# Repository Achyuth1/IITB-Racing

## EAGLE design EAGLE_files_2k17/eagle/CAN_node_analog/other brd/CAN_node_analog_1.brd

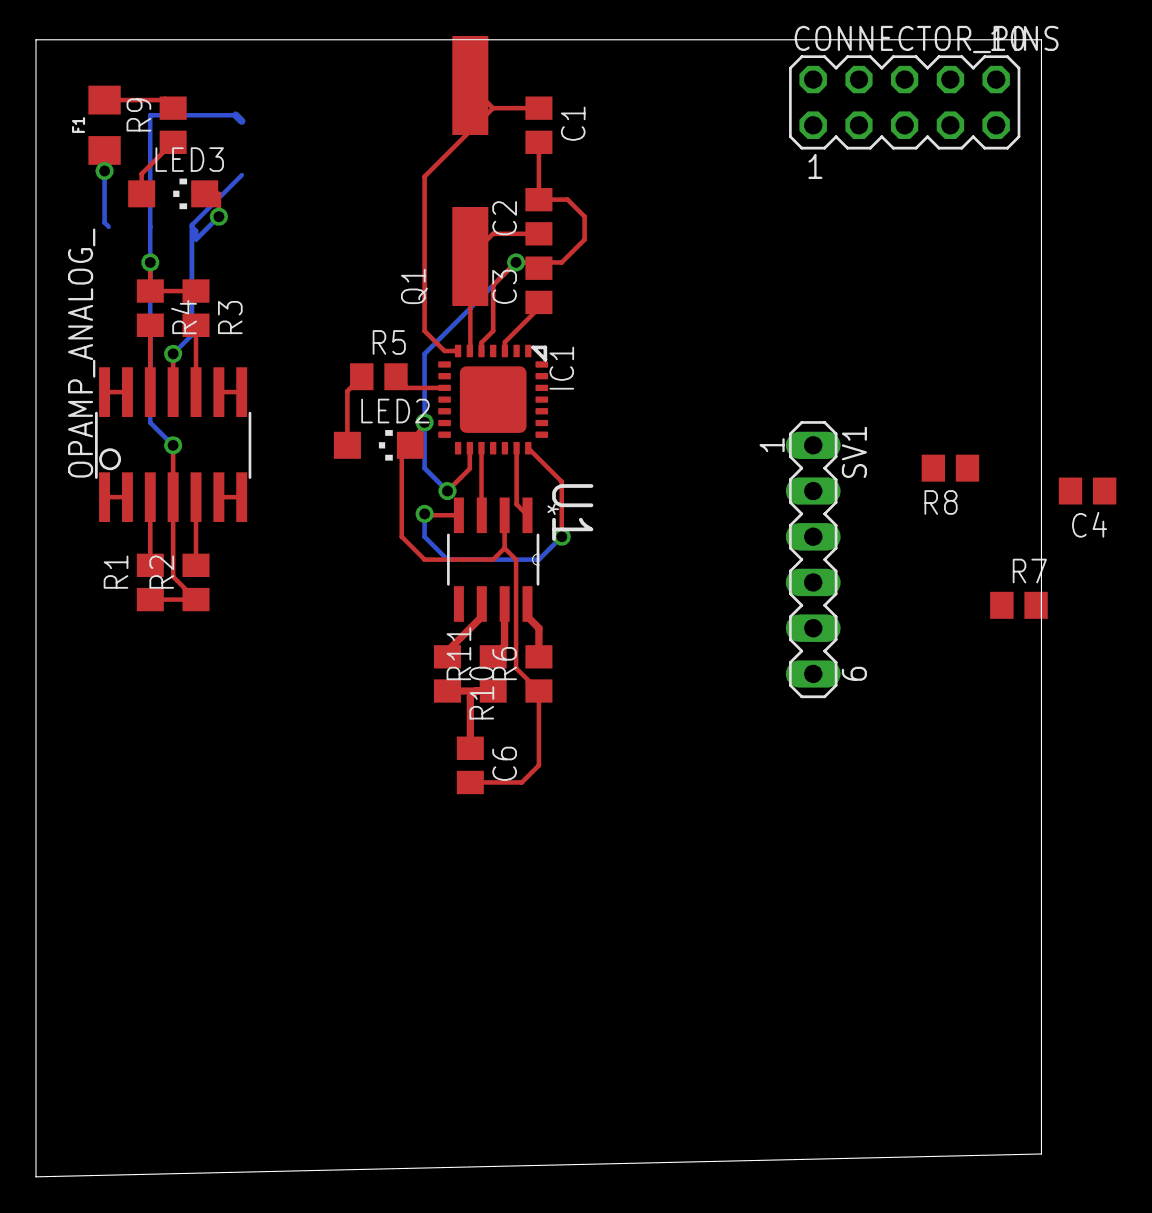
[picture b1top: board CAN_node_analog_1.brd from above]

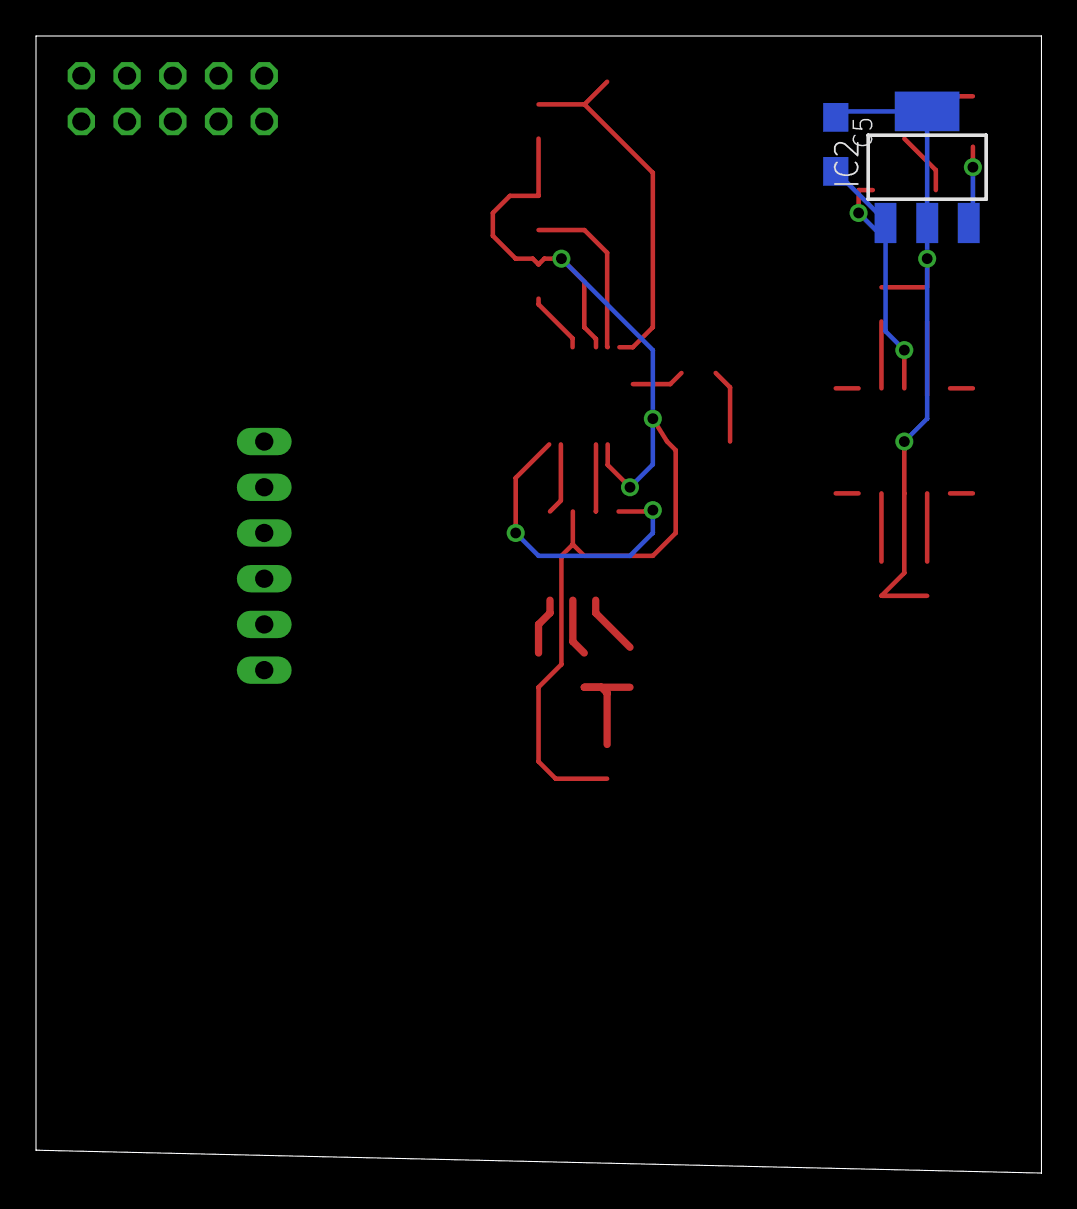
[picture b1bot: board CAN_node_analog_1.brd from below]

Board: 2 copper layers, 55.9 x 63.2 mm, 27 parts (2 on the bottom side), 29 nets.

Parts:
C1, C2, C4: 22pF; C0805
C3, C6: 10uF; C0805
C5: SMC_A
CONNECTOR_PINS: MA05-2
F1: 6V/0.5A; 1206
IC1: MICROCHIP_PIC18F2580-I/ML; MICROCHIP_QFN28-ML_6X6MM
IC2: LM1117IMPX-ADJ; SOT223
LED2, LED3: CHIPLED_1206
OPAMP_ANALOG_: ADWAITFS_LMC6464; ADWAITFS_SO14_LONGPADS
Q1: CSM-7X-DU
R1, R2, R3, R4: 47k; R0805
R5, R9: 1k; R0805
R6: 4k7; R0805
R7: 470; R0805
R8: 10k; R0805
R10, R11: 60E; R0805
SV1: MA06-1
U1: TEXAS-INSTRUMENTS_BY_ELEMENT14_BATCH_1_SN65HVD105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; TEXAS-INSTRUMENTS_BY_ELEMENT14_BATCH_1_SOIC127P600X175-8N

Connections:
5V: C5.+, CONNECTOR_PINS.3, IC1.17, IC2.2, IC2.TAB, OPAMP_ANALOG_.4, R1.1, R2.1, R3.1, R4.1, R8.2, SV1.2, U1.3
12V: CONNECTOR_PINS.10, F1.2, R9.2
ANALOG_1: CONNECTOR_PINS.8, OPAMP_ANALOG_.3, R1.2
ANALOG_2: CONNECTOR_PINS.6, OPAMP_ANALOG_.5, R2.2
ANALOG_3: CONNECTOR_PINS.4, OPAMP_ANALOG_.10, R3.2
ANALOG_4: CONNECTOR_PINS.2, OPAMP_ANALOG_.12, R4.2
ANALOG_IN_1: IC1.27, OPAMP_ANALOG_.1, OPAMP_ANALOG_.2
ANALOG_IN_2: IC1.28, OPAMP_ANALOG_.6, OPAMP_ANALOG_.7
ANALOG_IN_3: IC1.1, OPAMP_ANALOG_.8, OPAMP_ANALOG_.9
ANALOG_IN_4: IC1.2, OPAMP_ANALOG_.13, OPAMP_ANALOG_.14
CAN_H: CONNECTOR_PINS.5, R11.2, U1.7
CAN_L: CONNECTOR_PINS.7, R10.1, U1.6
CAN_RX: IC1.21, U1.4
CAN_TX: IC1.20, U1.1
GND: C1.2, C2.2, C3.2, C4.2, C5.-, C6.2, CONNECTOR_PINS.1, CONNECTOR_PINS.9, IC1.5, IC1.16, IC2.1, LED2.C, LED3.C, OPAMP_ANALOG_.11, R6.1, SV1.3, U1.2
LED: IC1.10, R5.2
MCLR: IC1.26, R7.1, SV1.1
unnamed: LED2.A, R5.1
unnamed: R6.2, U1.8
unnamed: C4.1, R7.2, R8.1
unnamed: F1.1, IC2.3
unnamed: LED3.A, R9.1
unnamed: C6.1, R10.2, R11.1
OSC1: C2.1, IC1.6, Q1.1
OSC2: C1.1, IC1.7, Q1.2
PGC: IC1.24, SV1.5
PGD: IC1.25, SV1.4
PGM: IC1.23, SV1.6
VCAP: C3.1, IC1.3

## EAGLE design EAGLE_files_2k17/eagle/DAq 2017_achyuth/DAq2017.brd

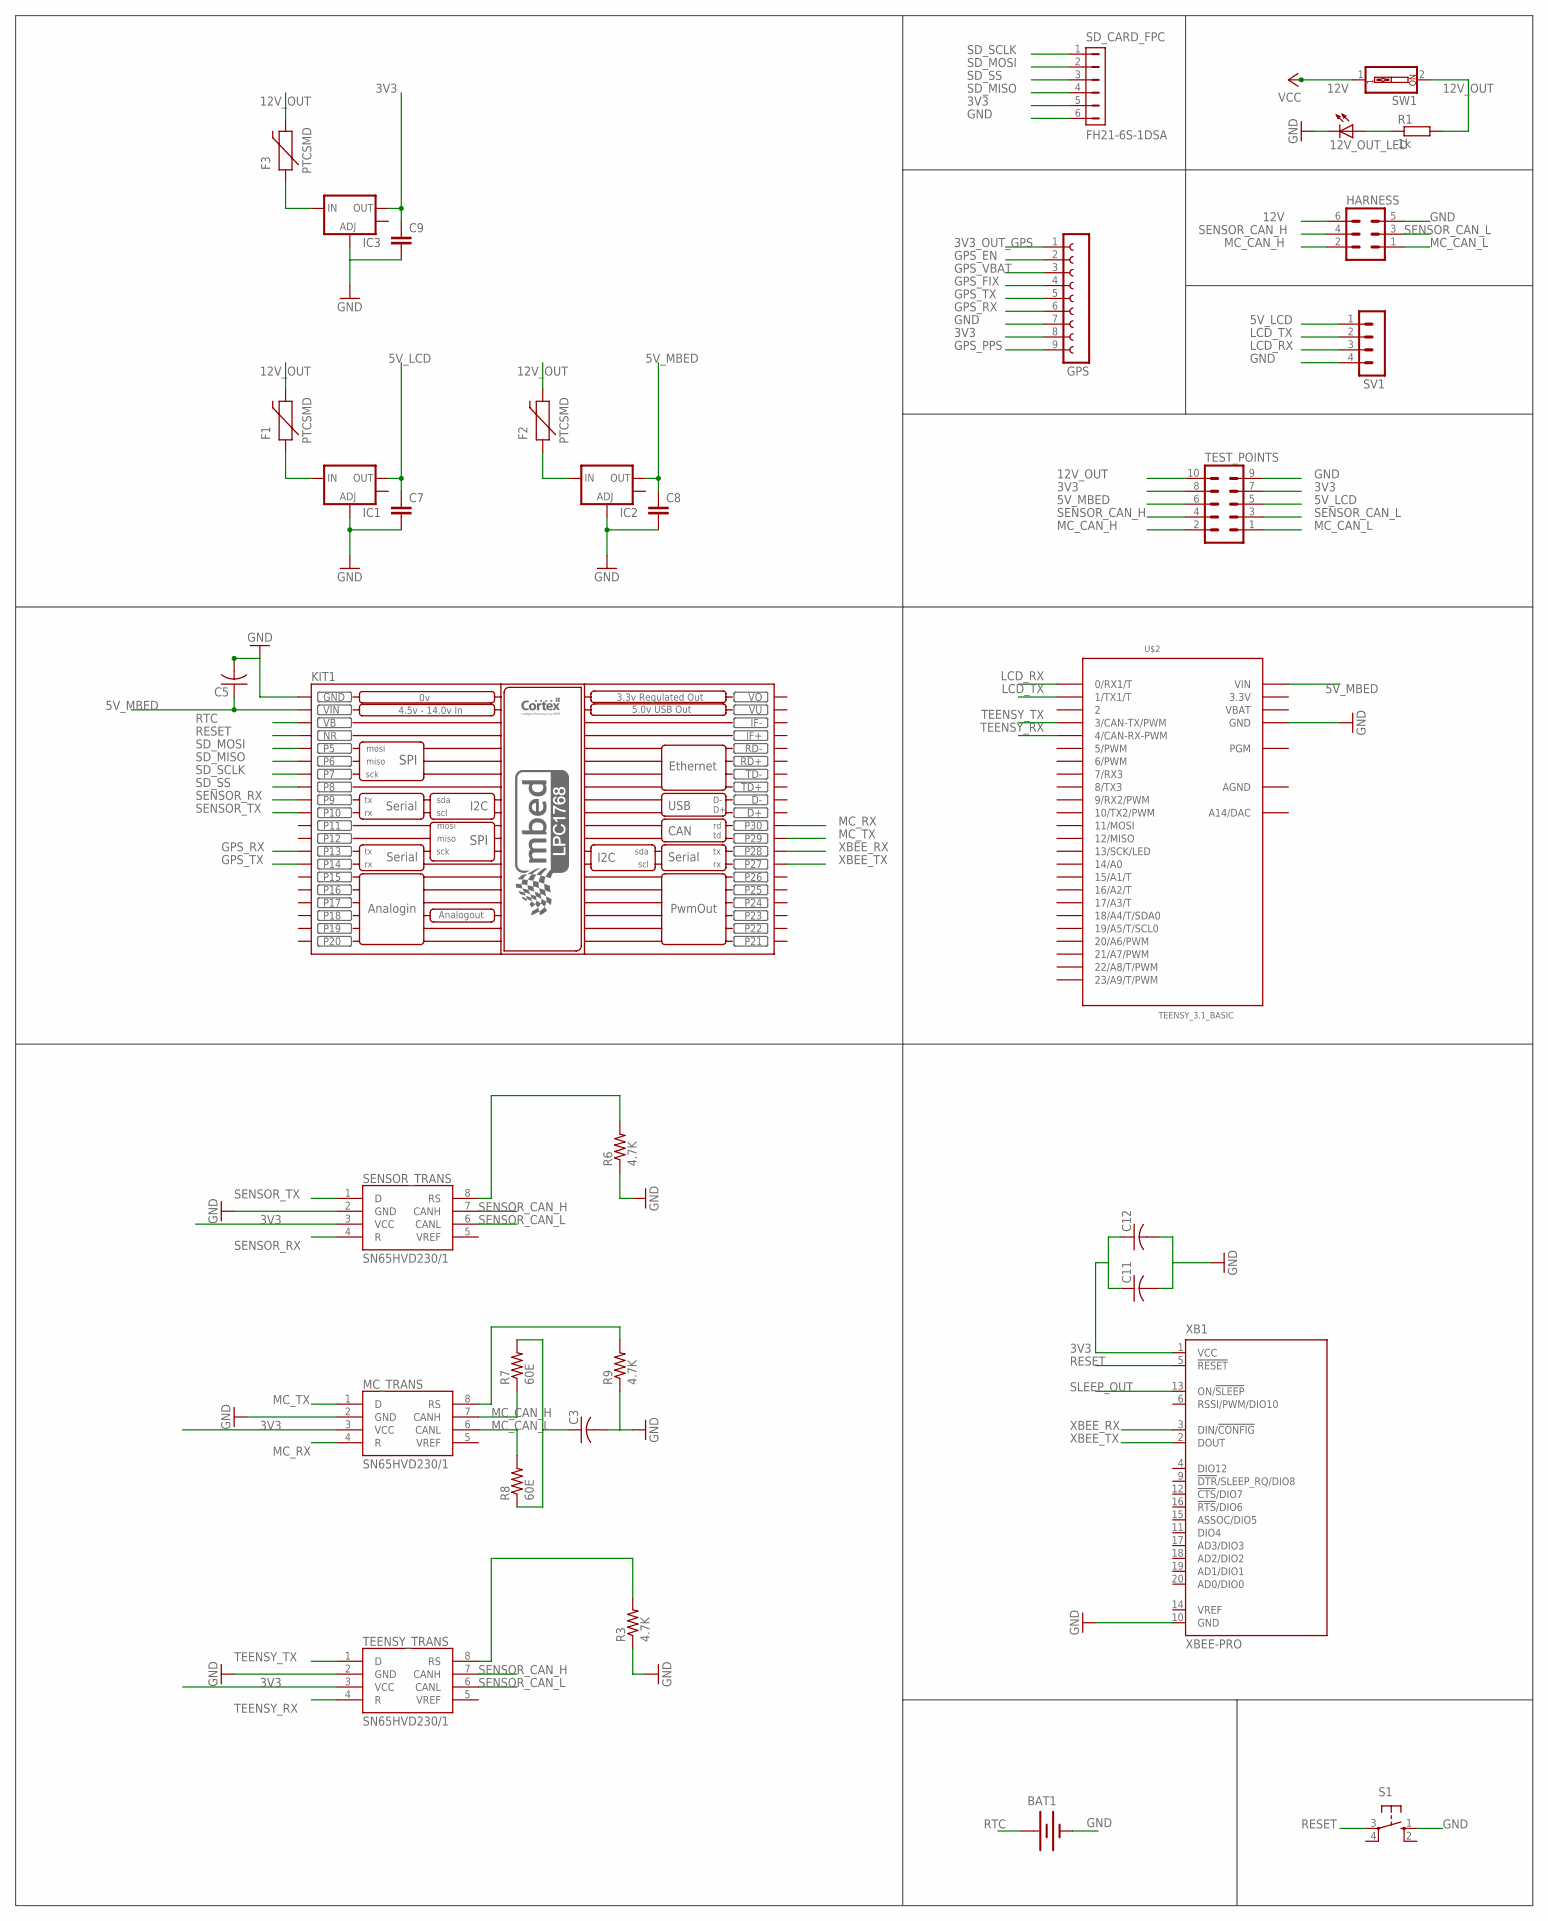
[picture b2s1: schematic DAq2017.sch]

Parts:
12V_OUT_LED: LEDCHIPLED_1206; CHIPLED_1206
BAT1: BATTERY20PTH; BATTCOM_20MM_PTH
C3, C5, C11, C12: C-USC0805; C0805
C7, C8, C9: C-EUC0805; C0805
F1, F2, F3: PTCSMD; PTC-1206
GPS: FE09-1; FE09
HARNESS: MA03-2
IC1, IC2, IC3: V_REG_LM1117SOT223; SOT223
KIT1: MBED_NXP_LPC1768; MBED-KIT
MC_TRANS: SN65HVD230/1; SO8
R1: 1k; R0805
R3, R6, R9: 4.7K; R0805
R7, R8: 60E; R0805
S1: 10-XX; B3F-10XX
SD_CARD_FPC: FH21-6S-1DSA
SENSOR_TRANS: SN65HVD230/1; SO8
SV1: MA04-1
SW1: SW_DIP-1; EDG-01
TEENSY_TRANS: SN65HVD230/1; SO8
TEST_POINTS: MA05-2
U$2: TEENSY_3.1_BASIC
XB1: XBEE-PRO

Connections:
3V3: C9.1, C11.1, C12.1, GPS.8, IC3.2 (OUT), MC_TRANS.3 (VCC), SD_CARD_FPC.5, SENSOR_TRANS.3 (VCC), TEENSY_TRANS.3 (VCC), TEST_POINTS.7, TEST_POINTS.8, XB1.1 (VCC)
3V3_OUT_GPS: GPS.1
5V_LCD: C7.1, IC1.2 (OUT), SV1.1, TEST_POINTS.5
5V_MBED: C5.1, C8.1, IC2.2 (OUT), KIT1.VIN, TEST_POINTS.6, U$2.VIN; also elsewhere on the board
12V: HARNESS.6, SW1.1
12V_OUT: F1.2, F2.2, F3.2, R1.2, SW1.2, TEST_POINTS.10
GND: 12V_OUT_LED.C, BAT1.2 (-), C3.2, C5.2, C7.2, C8.2, C9.2, C11.2, C12.2, GPS.7, HARNESS.5, IC1.1 (ADJ), IC2.1 (ADJ), IC3.1 (ADJ), KIT1.GND, MC_TRANS.2 (GND), R3.1, R6.1, R9.1, S1.1 (S), SD_CARD_FPC.6, SENSOR_TRANS.2 (GND), SV1.4, TEENSY_TRANS.2 (GND), TEST_POINTS.9, U$2.GND, XB1.10 (GND); also elsewhere on the board
GPS_EN: GPS.2
GPS_FIX: GPS.4
GPS_PPS: GPS.9
GPS_RX: GPS.6, KIT1.P$13 (P13)
GPS_TX: GPS.5, KIT1.P$14 (P14)
GPS_VBAT: GPS.3
LCD_RX: SV1.3, U$2.0 (0/RX1/T); also elsewhere on the board
LCD_TX: SV1.2, U$2.1 (1/TX1/T); also elsewhere on the board
MC_CAN_H: HARNESS.2, MC_TRANS.7 (CANH), R7.1, TEST_POINTS.2
MC_CAN_L: HARNESS.1, MC_TRANS.6 (CANL), R8.2, TEST_POINTS.1
MC_RX: KIT1.P$30 (P30), MC_TRANS.4 (R)
MC_TX: KIT1.P$29 (P29), MC_TRANS.1 (D)
unnamed: R3.2, TEENSY_TRANS.8 (RS)
unnamed: 12V_OUT_LED.A, R1.1
unnamed: R6.2, SENSOR_TRANS.8 (RS)
unnamed: C3.1, R7.2, R8.1
unnamed: MC_TRANS.8 (RS), R9.2
unnamed: F1.1, IC1.3 (IN)
unnamed: F2.1, IC2.3 (IN)
unnamed: F3.1, IC3.3 (IN)
RESET: KIT1.NR, S1.3, XB1.5 (!RESET)
RTC: BAT1.1 (+), KIT1.VB
SD_MISO: KIT1.P$6 (P6), SD_CARD_FPC.4
SD_MOSI: KIT1.P$5 (P5), SD_CARD_FPC.2
SD_SCLK: KIT1.P$7 (P7), SD_CARD_FPC.1
SD_SS: KIT1.P$8 (P8), SD_CARD_FPC.3
SENSOR_CAN_H: HARNESS.4, SENSOR_TRANS.7 (CANH), TEENSY_TRANS.7 (CANH), TEST_POINTS.4
SENSOR_CAN_L: HARNESS.3, SENSOR_TRANS.6 (CANL), TEENSY_TRANS.6 (CANL), TEST_POINTS.3
SENSOR_RX: KIT1.P$9 (P9), SENSOR_TRANS.4 (R)
SENSOR_TX: KIT1.P$10 (P10), SENSOR_TRANS.1 (D)
SLEEP_OUT: XB1.13 (ON/!SLEEP)
TEENSY_RX: TEENSY_TRANS.4 (R), U$2.4 (4/CAN-RX-PWM); also elsewhere on the board
TEENSY_TX: TEENSY_TRANS.1 (D), U$2.3 (3/CAN-TX/PWM); also elsewhere on the board
VO: KIT1.VOUT (VO)
VU: KIT1.VU
XBEE_RX: KIT1.P$28 (P28), XB1.3 (DIN/!CONFIG)
XBEE_TX: KIT1.P$27 (P27), XB1.2 (DOUT)

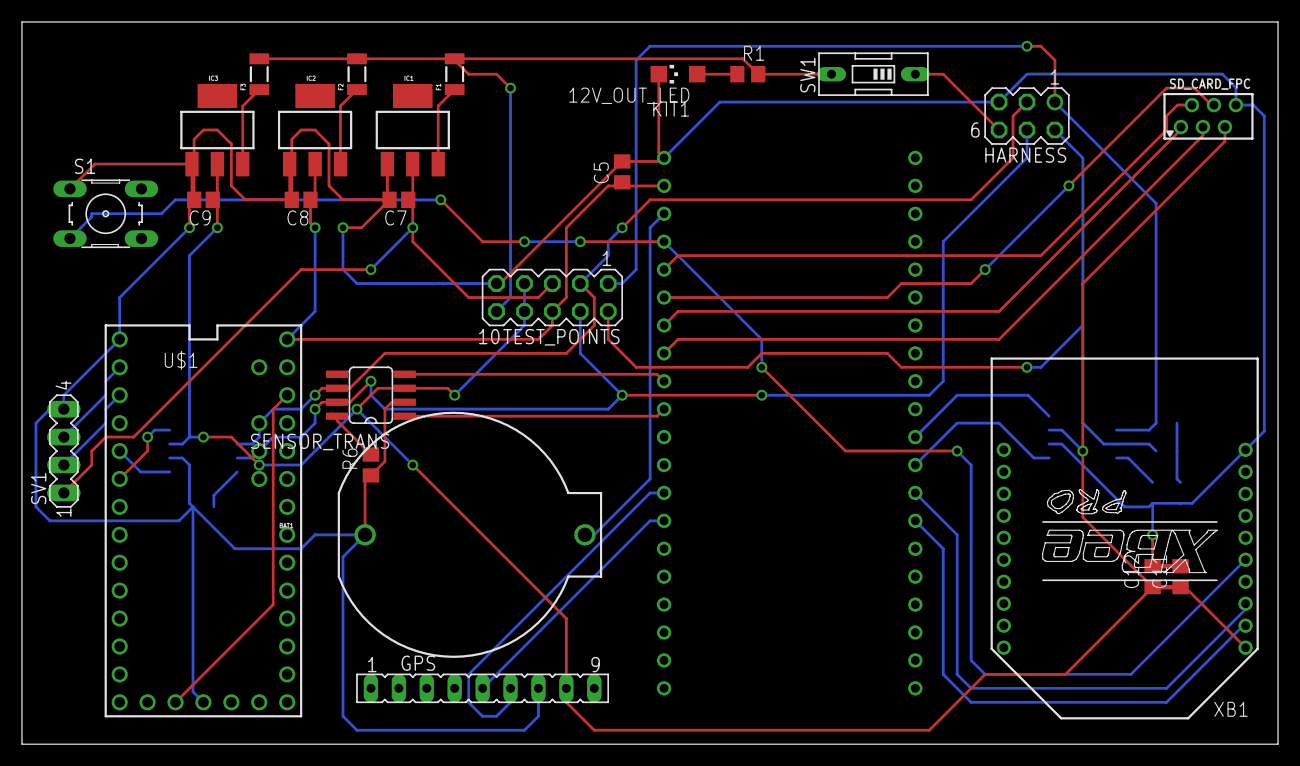
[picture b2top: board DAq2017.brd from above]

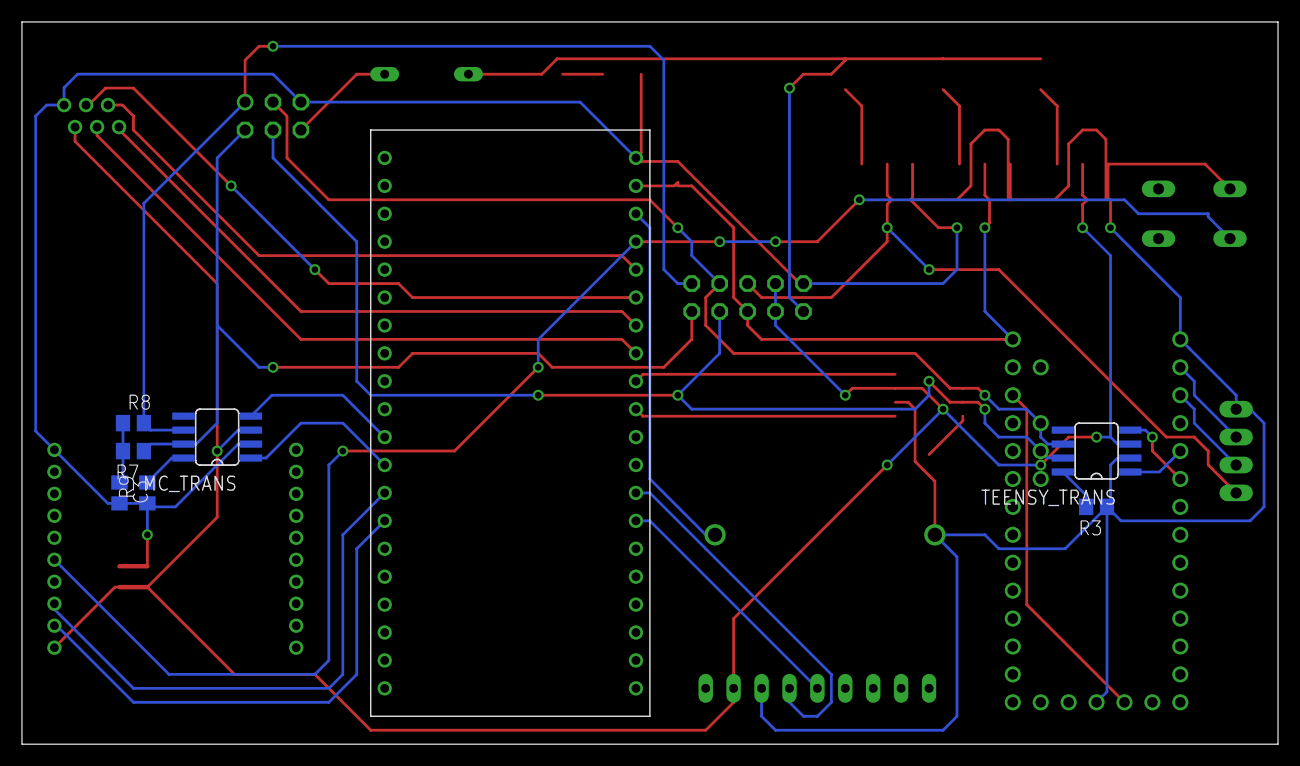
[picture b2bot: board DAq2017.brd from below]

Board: 2 copper layers, 114.3 x 65.7 mm, 34 parts (7 on the bottom side), 37 nets.

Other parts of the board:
U$1: TEENSY_3.1_ALL_PINS; TEENSY3-ALL_PINS

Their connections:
3.3V: U$1.3.3V, U$1.3.3V1
5V_MBED: U$1.VIN; also elsewhere on the board
GND: U$1.GND, U$1.GND1; also elsewhere on the board
LCD_RX: U$1.0; also elsewhere on the board
LCD_TX: U$1.1; also elsewhere on the board
TEENSY_RX: U$1.4; also elsewhere on the board
TEENSY_TX: U$1.3; also elsewhere on the board

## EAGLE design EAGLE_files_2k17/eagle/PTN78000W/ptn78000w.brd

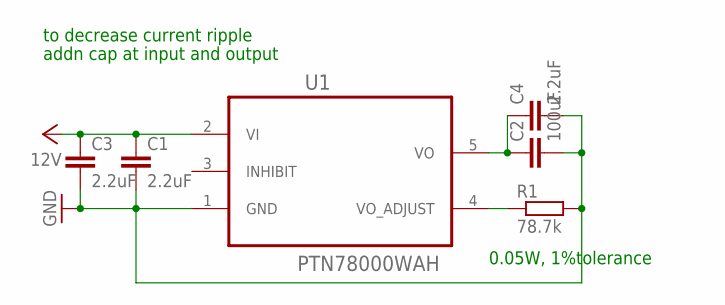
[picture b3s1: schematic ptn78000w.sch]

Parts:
C1, C3, C4: 2.2uF; C0805
C2: 100uF; C0805
R1: 78.7k; R0805
U1: PTN78000WAH; TI_PTN78000WAH

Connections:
GND: C1.2, C2.2, C3.2, C4.2, R1.2, U1.1 (GND)
unnamed: R1.1, U1.4 (VO_ADJUST)
unnamed: C2.1, C4.1, U1.5 (VO)
VCC: C1.1, C3.1, U1.2 (VI)

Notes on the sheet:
0.05W, 1%tolerance
to decrease current ripple
addn cap at input and output

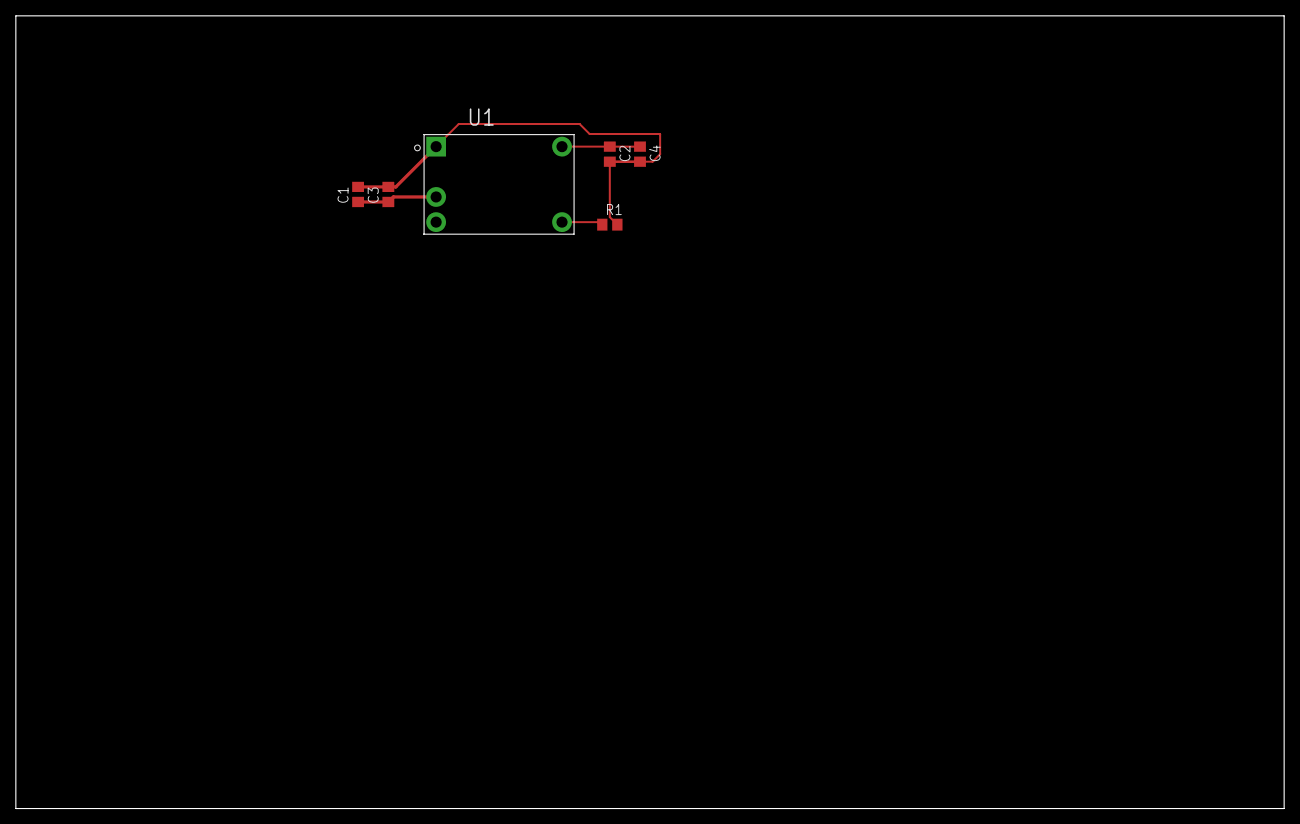
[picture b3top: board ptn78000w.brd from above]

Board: 2 copper layers, 160.0 x 100.0 mm, 6 parts (0 on the bottom side), 4 nets.

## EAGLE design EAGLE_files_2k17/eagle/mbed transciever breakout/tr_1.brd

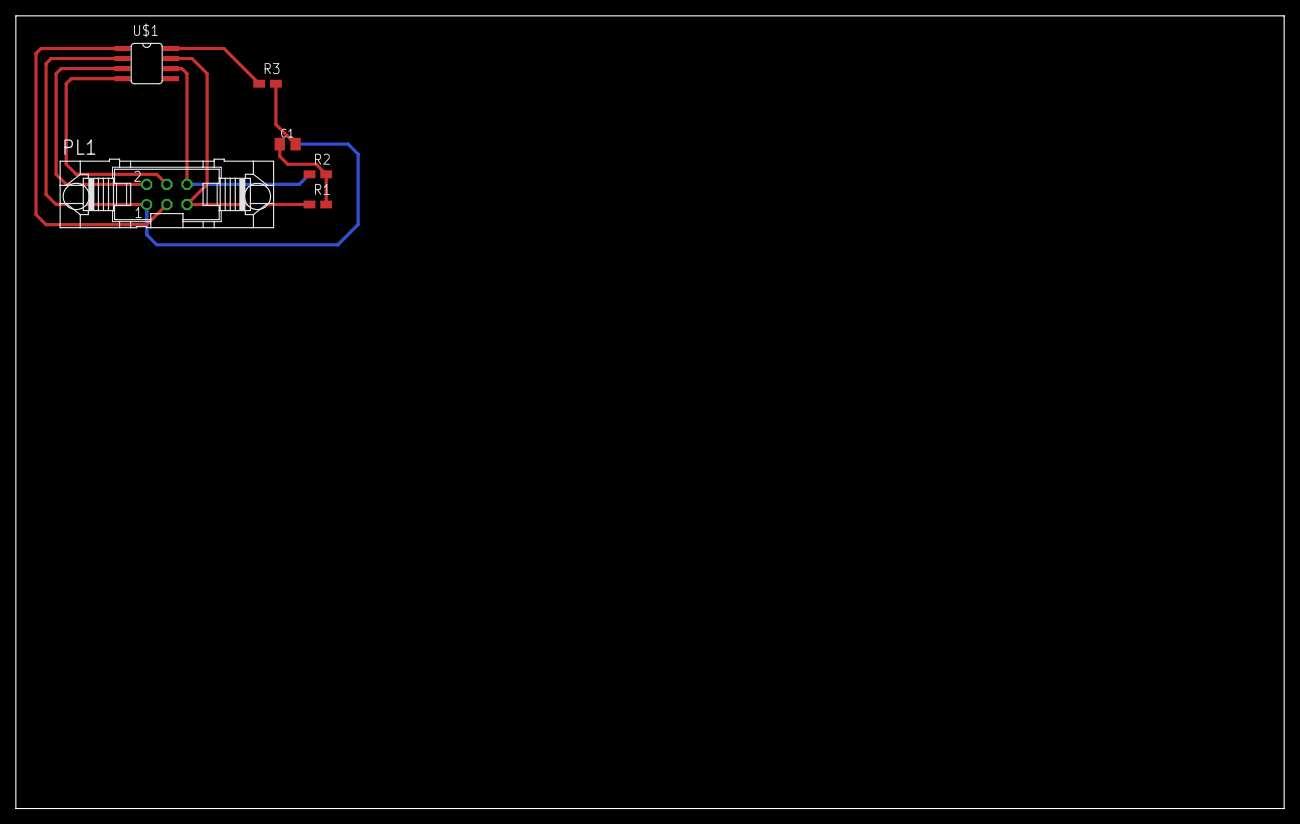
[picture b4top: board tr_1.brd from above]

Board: 2 copper layers, 160.0 x 100.0 mm, 6 parts (0 on the bottom side), 8 nets.

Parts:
C1: C0805K
PL1: 06V
R1, R2: 60E; R0805W
R3: 4.7k; R0805W
U$1: SN65HVD230/1; SO8

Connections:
CAN_H: PL1.5, R1.1, U$1.7
CAN_L: PL1.6, R2.1, U$1.6
CAN_RX: PL1.4, U$1.4
CAN_TX: PL1.3, U$1.1
GND: C1.2, PL1.1, R3.2, U$1.2
unnamed: R3.1, U$1.8
unnamed: C1.1, R1.2, R2.2
VCC: PL1.2, U$1.3

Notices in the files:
parts and their libraries:
sparkfun_fuses: Licensing: Creative Commons ShareAlike 4.0 International - https://creativecommons.org/licenses/by-sa/4.0
SparkFun-Electromechanical: Licensing: CC v3.0 Share-Alike You are welcome to use this library for commercial purposes.
